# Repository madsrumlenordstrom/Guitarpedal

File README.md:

## An open source distortion pedal
The design is all analog and uses diodes to distort the input signal.
It has 3 different modes of distortion. It is possible to either use germanium, silicon or LED's in the hard clipping stage. It is also possible to just use soft clipping.

The PCB is four layers since it so mouch nicer to work with and has become so cheap that two layer PCB are more or less obsolete. I wanted every component to be on the PCB and not having to deal with soldering extra wires to connectors and pots. So when every component is soldered to the PCB, the pedal is essentially done, and just needs to be put into an enclosure. Instead of having a enclosure with art on I designed the PCB to be aesthetically pleasing.

I using an acryllic plate as the lid on an aluminium enclosure, so the PCB is visible. As you can see on the pictures grease and dust becomes very visible on the acryllic lid. Acryllic is also a pain to work with as it is very brittle and can more or less only be cut out nicely on a CO2 laser. Next time I will probably find another material. However I do think the final product turned out nicely!

More pictures can be found in the pictures folder.
Personally I don't play any intrusments. This projects was made as a gift for family and friends. People who have been gifted this pedal like and generally think it sounds good, so I am quite satisfied with the result.

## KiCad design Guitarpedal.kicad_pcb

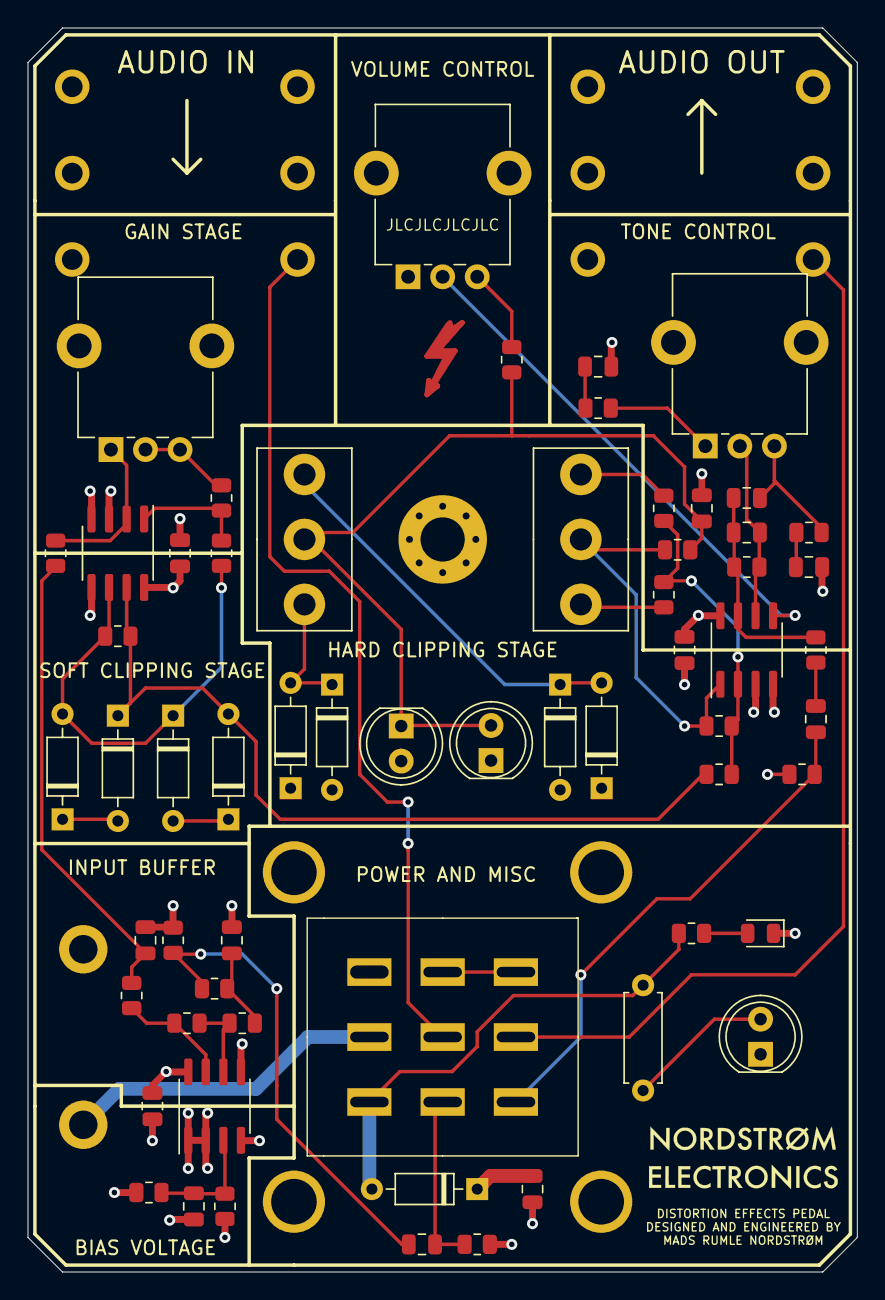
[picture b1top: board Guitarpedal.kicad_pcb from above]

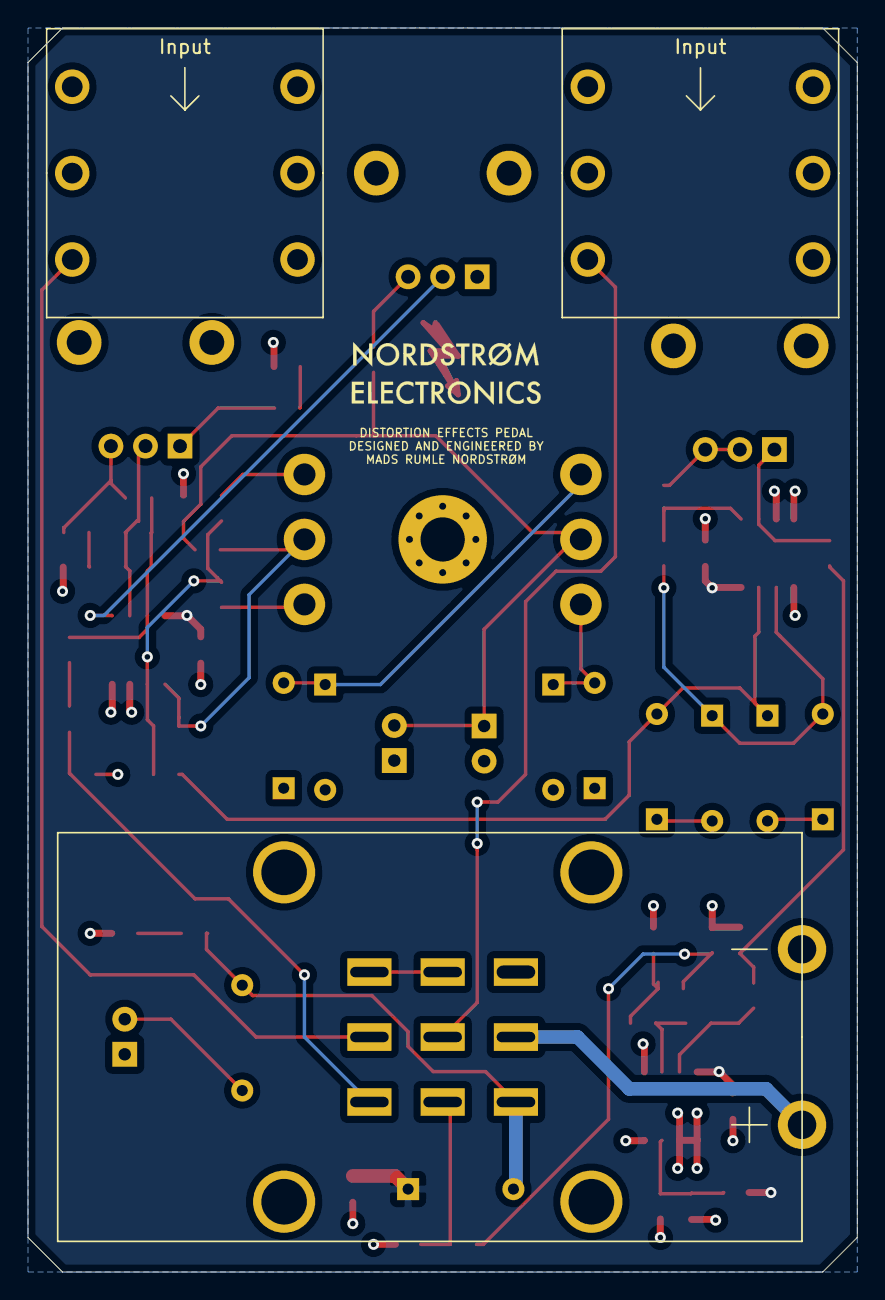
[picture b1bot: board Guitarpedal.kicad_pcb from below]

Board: 4 copper layers, 60.0 x 90.0 mm, 65 parts (3 on the bottom side), 41 nets.

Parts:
BT1: Battery_Cell; 9V_Battery_Holder_1294
C1, C11, C15: 10u; C_0805_2012Metric
C2, C3, C4, C6, C13, C14: 100n; C_0805_2012Metric
C7: 10n; C_0805_2012Metric
C8: 33n; C_0805_2012Metric
C9: 47p; C_0805_2012Metric
C10: 1n; C_0805_2012Metric
C12: 3.3n; C_0805_2012Metric
D1, D3, D4: D_Schottky; D_DO-35_SOD27_P7.62mm_Horizontal
D2: LED; LED_0805_2012Metric
D5, D6, D9, D10, D11, D12: 1N4148; D_DO-35_SOD27_P7.62mm_Horizontal
D7, D8, D13: LED; LED_D5.0mm
H1: MountingHole_Pad; MountingHole_3.2mm_M3_Pad_Via
J1, J2: AudioJack2; ACJM-IH
R1, R6: 649; R_0805_2012Metric
R2, R3: 102k; R_0805_2012Metric
R4: 26.7k; R_0805_2012Metric
R5: 16.9k; R_0805_2012Metric
R7, R8, R9: 10k; R_0805_2012Metric
R10, R16: 40.2k; R_0805_2012Metric
R11, R18: 931k; R_0805_2012Metric
R12: 499k; R_0805_2012Metric
R13: 80.6k; R_0805_2012Metric
R14: 24.9k; R_0805_2012Metric
R15: 4.99k; R_0805_2012Metric
R17: 1k; R_0805_2012Metric
R19: 17.4k; R_0805_2012Metric
R20: 56.2k; R_0805_2012Metric
R21: 6.81k; R_0805_2012Metric
R22: 3.24k; R_0805_2012Metric
R23: 22.1k; R_0805_2012Metric
R24: 1.2k; R_Axial_DIN0207_L6.3mm_D2.5mm_P7.62mm_Horizontal
R25: 105k; R_0805_2012Metric
RV1: 1M; Potentiometer_Alpha_RD901F-40-00D_Single_Vertical_CircularH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
RV2: 100k; Potentiometer_Alpha_RD901F-40-00D_Single_Vertical_CircularH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
RV3: 50k; Potentiometer_Alpha_RD901F-40-00D_Single_Vertical_CircularH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
SW1, SW2: SW_SPDT; 100SP1T1B4M2QE
U1, U2, U3: TL072; SOIC-8_3.9x4.9mm_P1.27mm
U4: 3PDT_footswitch; 3PDT

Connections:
4V5: C9.1, C10.1, D3.2, D4.1, D5.2, D6.1, D7.2, D8.1, R12.2, RV2.1, U1.1, U1.2, U1.5, U2.3, U2.5, U3.3
+9V: C1.2, C2.2, C3.2, C4.2, D1.1, R2.1, U1.8, U2.8, U3.8
Audio_in: C7.2, R11.1, U4.6
Buffer_out: C10.2, R9.2, R16.1
GND: BT1.2, C1.1, C2.1, C3.1, C4.1, C6.1, C8.1, C14.1, C15.1, D2.1, D13.1, H1.1, J1.S, J2.S, R3.2, R11.2, R18.2, U1.4, U2.4, U3.4
Gain_out: R15.2, R23.1, U2.1
Hard_clipping_out: C8.2, D7.1, D8.2, R6.2, R25.1, SW2.2
unnamed: BT1.1, U4.2
unnamed: C6.2, R2.2, R3.1, U1.3
unnamed: C7.1, R7.1, R12.1
unnamed: C9.2, R7.2, R8.1
unnamed: C11.2, R17.2
unnamed: C12.1, C13.2, R17.1, R19.2, U3.7
unnamed: C12.2, R19.1, RV3.2, U3.6
unnamed: C13.1, R22.1, RV3.3
unnamed: C14.2, R21.1
unnamed: C15.2, R22.2
unnamed: D2.2, R1.2
unnamed: D3.1, D4.2, SW2.1
unnamed: D5.1, D6.2, SW2.3
unnamed: D9.1, D10.2
unnamed: D9.2, D11.1, R20.1, R23.2, U2.6
unnamed: D11.2, D12.1
unnamed: D13.2, R24.2
unnamed: J1.T, U4.5
unnamed: J2.T, U4.8
unnamed: R4.1, R8.2, U1.6
unnamed: R4.2, R9.1, U1.7
unnamed: R5.2, SW1.3
unnamed: R5.1, R10.1, R13.1, R14.2, U3.2
unnamed: R10.2, SW1.1
unnamed: R6.1, R13.2, SW1.2, U3.1
unnamed: R15.1, RV1.2, RV1.3
unnamed: R16.2, RV1.1, U2.2
unnamed: R21.2, RV3.1
unnamed: R25.2, RV2.3
unnamed: RV2.2, U3.5
unnamed: U4.4, U4.7
Power_in: D1.2, R1.1, R24.1, U4.3
Soft_clipping_out: D10.1, D12.2, R14.1, R20.2, U2.7
Tone_control_out: C11.1, R18.1, U4.9

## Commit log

2021-12-23 First version
2022-05-11 Updated to 6.0
2022-05-11 Cleaned up repo
2022-05-11 Added readme and pictures
2022-05-11 More about the project
